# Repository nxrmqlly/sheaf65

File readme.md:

# sheaf65 🌊

A barebones, hackable, opinionated, ansi 65% layout  keyboard. The `Backspace` key and the `Grave` key swapped due to personal preferences.

The Keyboard is designed to be very bare bones and it is basically 3 layers - The switchplate (top), The PCB (Middle),
and The Backplate (Bottom) - kind of like a sandwich mounted keyboard.

The switchplate ("plate") and the backplate are to be 3D printed and engineered.
The whole "sandwich" is held together with 10 M2x10mm brass spacers and one M2x6mm brass spacer.

I also took the liberty to add two knobs and an OLED display to the keyboard because... why not?

## TL;DR for busy people

A simple, hackable 65% keyboard
1. RP2040-powered
2. Fully Hotswap (TTC Pokayoke V2)
3. 0.91" OLED Screen
4. Dual Rotary Encoders (Knobs)
5. QMK firmware (VIA soon)
6. Sandwich Mounted (3-stacked-layer)

Built because I wanted something fun and unique... with knobs.

## Why?
I wanted a nice keyboard, and decided that making one for myself would be a fun challenge to pursue.
I wanted a unique yet sleek looking keyboard that somewhat resembles the idea of a through hole keybaord kit minus the ugly visible diodes.
Also, no such THT keyboard kit did hotswap sockets (I know the sockets are SMD but you get me) so there's that.

## Microcontroller / Devboard
I used an Generic ProMicro RP2040 chip which is basically an Pi RP2040 in a somewhat a ProMicro layout, I found it on robu and I thought it was perfect so I went with it!. 

The devboard is THT soldered and mounted onto the keyboard, in full display, sort of like nibble65 keyboard but horizontal.

## The PCB

The PCB was made in the best software ever (for legal reasons that's a joke) called **KiCad**, it was straightforward enough but I think a good software helps a ton! Also, I'm taking on SMD soldering by including TTC Pokayoke hotswap sockets in this!

Here are some screenshots:

| What               | Image                               |
|--------------------|-------------------------------------|
| Schematic          | |
| PCB (B.silk hidden)|             |
| PCB 3D Model       ||

## The "Case"

I designed the case in Autodesk Fusion (formerly Fusion360) - good software!
The case is not really a case, its just two plates, one backplate and one switchplate

| What               | Image                                        |
|--------------------|----------------------------------------------|
| CAD Assembly       | |

## WTF is that design? (Design Credits + more)

The inspiration for this kind of keyboard case (or the whole thing in general) comes from though-hole keyboard kits like:
- mercuito40 (for the switchplate and mounting)
- gingham65 (mounting)
- nibble65 (embracing the exposed MCU design)
- my wack brain (for two knobs)
- also thanks to [somepin](https://www.printables.com/@somepin) for the [3d printed keyboard feet](https://www.printables.com/model/876658-mechanical-keyboard-cone-feet/files)
- **Honorable mention:**
>*reviewer (#fallout-checkpoint): ...I also think this would look sick with under glow... maybe consider that*
>Yeah no, the keyboard was NoRGB by choice, I like NoRGB setups

However, I didn't really like the exposed ugly diodes on the top, so I opted for a neat silkscreen instead which I designed in **Figma** (I know it isnt the correct tool for the job but whatever really)

> (find the custom silkscreen footprints [here](./kicad/footprints/art.pretty/))

## Keyboard Parts

Straightforward really, the switches, keycaps - they're all personal preference, so, heres my preference:

1. **Switches**: Nothing really beats the **Keygeek x MZ Y3 Linear Switches** for me, they're the perfect mix of thock (not as much as the Y2) and just enough creamy sound
2. **Keycaps**: PBT Clone Keycaps, nothing technical here, just Cherry Profile because I'm boring.
3. **Stabilizers**: i may have cheaped out, but the **Durock Plate-Mount Stabilizers** will work out for me.
4. **Hotswap**: The PCB is designed for TTC Pokayoke V2 hotswap sockets, so customizability is infinite!
5. **The "Case"**: The Hardware/CAD directory has both KeyboardPlate and Backplate STEP files, with their _3DP suffixed variants which are meant for 3D printing as they are filleted.

But really though, switches and keycaps are very personal and well, I can't really decide for you but all I can say is that I saw a thousand videos before settline on what I did.

## Firmware

Nothing too fancy here, just QMK (I fought with qmk for HOURS)

I plan to add VIA support soon :tm:

## The BOM

I would create a markdown table but I'm lazy... full breakdown in
[bom.csv here](./Hardware/bom/bom.csv)

> Costs \~₹10619 (~$124)

Somehow the BOM was fun to write!

## How to build it IRL

1. Spend some $$$ to get the parts from the BOM
2. Get your PCB fabricated and case 3D printed or machined (if 3D printing use the _3DP suffixed CAD files)
3. Solder Hotswap sockets on the back of the PCB and the through hole diodes too.
4. Solder header pins onto the MCU and that onto the PCB
5. Secure the 6mm stanoffs onto the countersunk holes on the backplate and the 10mm standoffs on the rest of the holes
6. Connect your switches to the plate and PCB
7. Slide the PCB into the standoffs and secure the plate with screws.

## License
The hardware (PCB, CAD Parts, Footprints) are licensed under `CERN Open Hardware Licence Version 2 - Strongly Reciprocal` 
which means, you're all-right to copy my work and use it in yours but you must disclose your source code and project files to opensource platforms if you use my work. See [LICENSE](LICENSE)

Firmware is QMK so, it is licensed under `GNU General Public License v2` (see [LICENSE-GPL](LICENSE-GPL))

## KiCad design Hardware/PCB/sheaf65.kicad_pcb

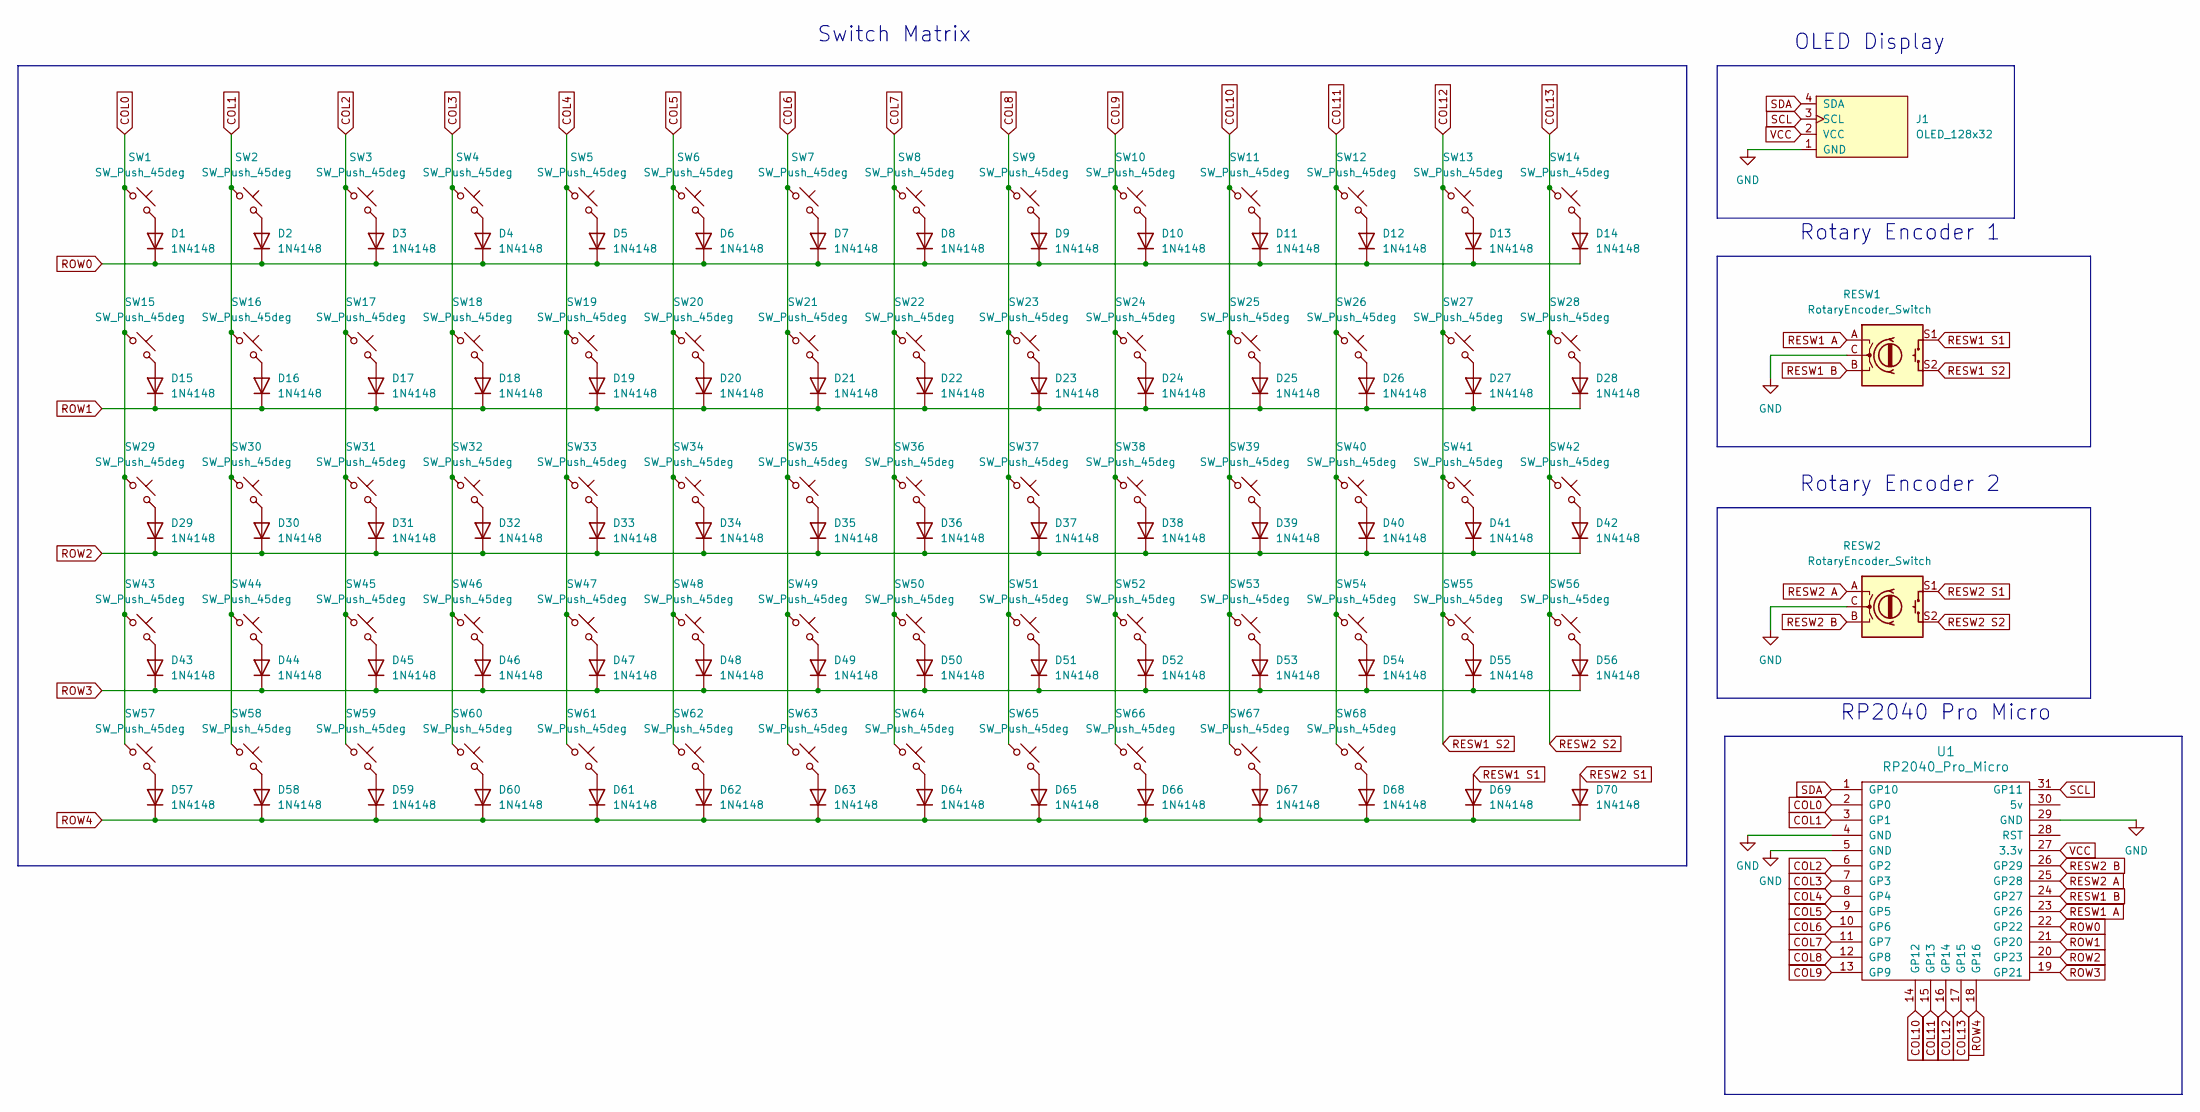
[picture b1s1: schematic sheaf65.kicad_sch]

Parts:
D1, D2, D3, D4, D5, D6, D7, D8, D9, D10, D11, D12, D13, D14, D15, D16, D17, D18, D19, D20, D21, D22, D23, D24, D25, D26, D27, D28, D29, D30, D31, D32, D33, D34, D35, D36, D37, D38, D39, D40, D41, D42, D43, D44, D45, D46, D47, D48, D49, D50, D51, D52, D53, D54, D55, D56, D57, D58, D59, D60, D61, D62, D63, D64, D65, D66, D67, D68, D69, D70: 1N4148; D_DO-35_SOD27_P7.62mm_Horizontal
J1: OLED_128x32; SSD1306-0.91-OLED-4pin-128x32
RESW1, RESW2: RotaryEncoder_Switch; RotaryEncoder_Alps_EC11E-Switch_Vertical_H20mm
SW1, SW2, SW3, SW4, SW5, SW6, SW7, SW8, SW9, SW10, SW11, SW12, SW13, SW15, SW17, SW18, SW19, SW20, SW21, SW22, SW23, SW24, SW25, SW26, SW27, SW28, SW30, SW32, SW33, SW34, SW35, SW36, SW37, SW38, SW39, SW40, SW41, SW42, SW44, SW46, SW47, SW48, SW49, SW50, SW51, SW52, SW53, SW54, SW55, SW57, SW58, SW63, SW64, SW65, SW66, SW67, SW68: SW_Push_45deg; SW_Hotswap_Kailh_MX_1.00u
SW14: SW_Push_45deg; SW_Hotswap_Kailh_MX_2.00u
SW16, SW29: SW_Push_45deg; SW_Hotswap_Kailh_MX_1.50u
SW31, SW56: SW_Push_45deg; SW_Hotswap_Kailh_MX_1.75u
SW43, SW45: SW_Push_45deg; SW_Hotswap_Kailh_MX_2.25u
SW59, SW60, SW61: SW_Push_45deg; SW_Hotswap_Kailh_MX_1.25u
SW62: SW_Push_45deg; SW_Hotswap_Kailh_MX_6.25u
U1: RP2040_Pro_Micro

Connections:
COL0: SW1.1, SW15.1, SW29.1, SW43.1, SW57.1, U1.2 (GP0)
COL1: SW2.1, SW16.1, SW30.1, SW44.1, SW58.1, U1.3 (GP1)
COL2: SW3.1, SW17.1, SW31.1, SW45.1, SW59.1, U1.6 (GP2)
COL3: SW4.1, SW18.1, SW32.1, SW46.1, SW60.1, U1.7 (GP3)
COL4: SW5.1, SW19.1, SW33.1, SW47.1, SW61.1, U1.8 (GP4)
COL5: SW6.1, SW20.1, SW34.1, SW48.1, SW62.1, U1.9 (GP5)
COL6: SW7.1, SW21.1, SW35.1, SW49.1, SW63.1, U1.10 (GP6)
COL7: SW8.1, SW22.1, SW36.1, SW50.1, SW64.1, U1.11 (GP7)
COL8: SW9.1, SW23.1, SW37.1, SW51.1, SW65.1, U1.12 (GP8)
COL9: SW10.1, SW24.1, SW38.1, SW52.1, SW66.1, U1.13 (GP9)
COL10: SW11.1, SW25.1, SW39.1, SW53.1, SW67.1, U1.14 (GP12)
COL11: SW12.1, SW26.1, SW40.1, SW54.1, SW68.1, U1.15 (GP13)
COL12: RESW1.S2, SW13.1, SW27.1, SW41.1, SW55.1, U1.16 (GP14)
COL13: RESW2.S2, SW14.1, SW28.1, SW42.1, SW56.1, U1.17 (GP15)
GND: J1.1 (GND), RESW1.C, RESW2.C, U1.4 (GND), U1.5 (GND), U1.29 (GND)
unnamed: D1.2 (A), SW1.2
unnamed: D2.2 (A), SW2.2
unnamed: D3.2 (A), SW3.2
unnamed: D4.2 (A), SW4.2
unnamed: D5.2 (A), SW5.2
unnamed: D6.2 (A), SW6.2
unnamed: D7.2 (A), SW7.2
unnamed: D8.2 (A), SW8.2
unnamed: D9.2 (A), SW9.2
unnamed: D10.2 (A), SW10.2
unnamed: D11.2 (A), SW11.2
unnamed: D12.2 (A), SW12.2
unnamed: D13.2 (A), SW13.2
unnamed: D14.2 (A), SW14.2
unnamed: D15.2 (A), SW15.2
unnamed: D16.2 (A), SW16.2
unnamed: D17.2 (A), SW17.2
unnamed: D18.2 (A), SW18.2
unnamed: D19.2 (A), SW19.2
unnamed: D20.2 (A), SW20.2
unnamed: D21.2 (A), SW21.2
unnamed: D22.2 (A), SW22.2
unnamed: D23.2 (A), SW23.2
unnamed: D24.2 (A), SW24.2
unnamed: D25.2 (A), SW25.2
unnamed: D26.2 (A), SW26.2
unnamed: D27.2 (A), SW27.2
unnamed: D28.2 (A), SW28.2
unnamed: D29.2 (A), SW29.2
unnamed: D30.2 (A), SW30.2
unnamed: D31.2 (A), SW31.2
unnamed: D32.2 (A), SW32.2
unnamed: D33.2 (A), SW33.2
unnamed: D34.2 (A), SW34.2
unnamed: D35.2 (A), SW35.2
unnamed: D36.2 (A), SW36.2
unnamed: D37.2 (A), SW37.2
unnamed: D38.2 (A), SW38.2
unnamed: D39.2 (A), SW39.2
unnamed: D40.2 (A), SW40.2
unnamed: D41.2 (A), SW41.2
unnamed: D42.2 (A), SW42.2
unnamed: D43.2 (A), SW43.2
unnamed: D44.2 (A), SW44.2
unnamed: D45.2 (A), SW45.2
unnamed: D46.2 (A), SW46.2
unnamed: D47.2 (A), SW47.2
unnamed: D48.2 (A), SW48.2
unnamed: D49.2 (A), SW49.2
unnamed: D50.2 (A), SW50.2
unnamed: D51.2 (A), SW51.2
unnamed: D52.2 (A), SW52.2
unnamed: D53.2 (A), SW53.2
unnamed: D54.2 (A), SW54.2
unnamed: D55.2 (A), SW55.2
unnamed: D56.2 (A), SW56.2
unnamed: D57.2 (A), SW57.2
unnamed: D58.2 (A), SW58.2
unnamed: D59.2 (A), SW59.2
unnamed: D60.2 (A), SW60.2
unnamed: D61.2 (A), SW61.2
unnamed: D62.2 (A), SW62.2
unnamed: D63.2 (A), SW63.2
unnamed: D64.2 (A), SW64.2
unnamed: D65.2 (A), SW65.2
unnamed: D66.2 (A), SW66.2
unnamed: D67.2 (A), SW67.2
unnamed: D68.2 (A), SW68.2
RESW1 A: RESW1.A, U1.23 (GP26)
RESW1 B: RESW1.B, U1.24 (GP27)
RESW1 S1: D69.2 (A), RESW1.S1
RESW2 A: RESW2.A, U1.25 (GP28)
RESW2 B: RESW2.B, U1.26 (GP29)
RESW2 S1: D70.2 (A), RESW2.S1
ROW0: D1.1 (K), D2.1 (K), D3.1 (K), D4.1 (K), D5.1 (K), D6.1 (K), D7.1 (K), D8.1 (K), D9.1 (K), D10.1 (K), D11.1 (K), D12.1 (K), D13.1 (K), D14.1 (K), U1.22 (GP22)
ROW1: D15.1 (K), D16.1 (K), D17.1 (K), D18.1 (K), D19.1 (K), D20.1 (K), D21.1 (K), D22.1 (K), D23.1 (K), D24.1 (K), D25.1 (K), D26.1 (K), D27.1 (K), D28.1 (K), U1.21 (GP20)
ROW2: D29.1 (K), D30.1 (K), D31.1 (K), D32.1 (K), D33.1 (K), D34.1 (K), D35.1 (K), D36.1 (K), D37.1 (K), D38.1 (K), D39.1 (K), D40.1 (K), D41.1 (K), D42.1 (K), U1.20 (GP23)
ROW3: D43.1 (K), D44.1 (K), D45.1 (K), D46.1 (K), D47.1 (K), D48.1 (K), D49.1 (K), D50.1 (K), D51.1 (K), D52.1 (K), D53.1 (K), D54.1 (K), D55.1 (K), D56.1 (K), U1.19 (GP21)
ROW4: D57.1 (K), D58.1 (K), D59.1 (K), D60.1 (K), D61.1 (K), D62.1 (K), D63.1 (K), D64.1 (K), D65.1 (K), D66.1 (K), D67.1 (K), D68.1 (K), D69.1 (K), D70.1 (K), U1.18 (GP16)
SCL: J1.3 (SCL), U1.31 (GP11)
SDA: J1.4 (SDA), U1.1 (GP10)
VCC: J1.2 (VCC), U1.27 (3.3v)

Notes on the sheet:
RP2040 Pro Micro
Rotary Encoder 2
Switch Matrix
Rotary Encoder 1
OLED Display

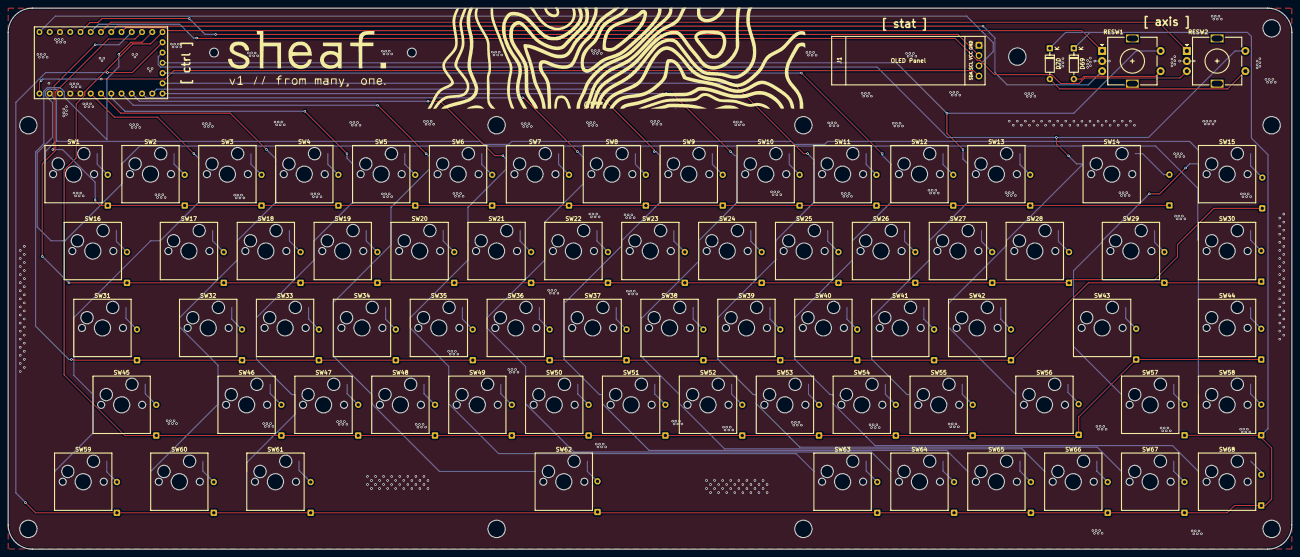
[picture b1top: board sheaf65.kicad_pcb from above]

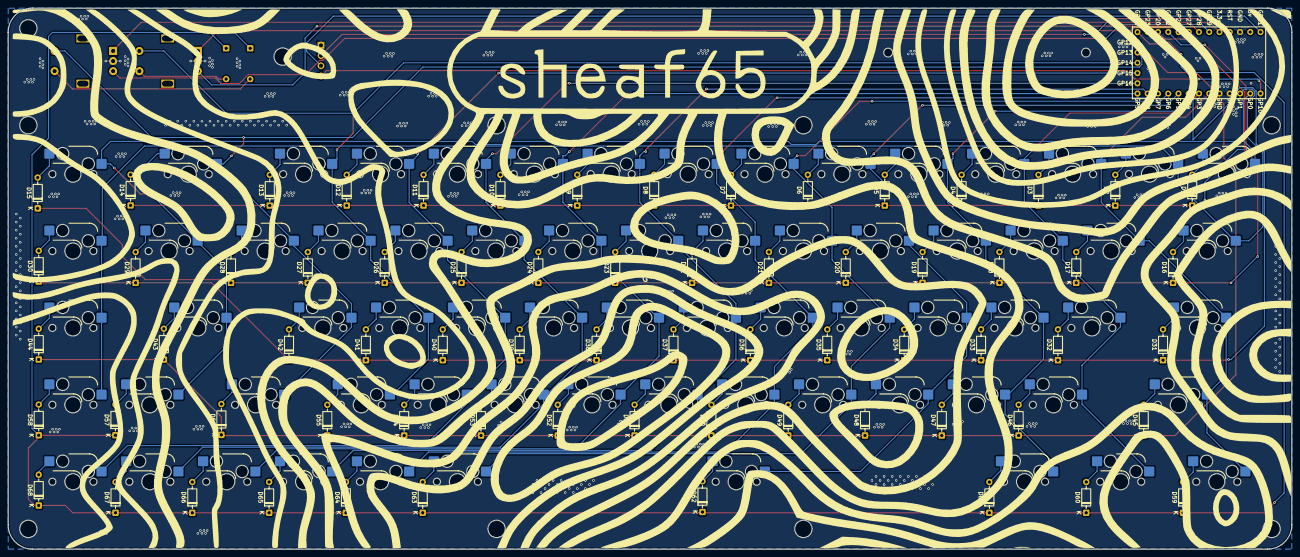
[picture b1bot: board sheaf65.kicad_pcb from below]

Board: 2 copper layers, 318.0 x 134.0 mm, 142 parts (68 on the bottom side), 97 nets.

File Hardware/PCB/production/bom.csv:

Designator,Footprint,Quantity,Value,LCSC Part #
"D1, D10, D11, D12, D13, D14, D15, D16, D17, D18, D19, D2, D20, D21, D22, D23, D24, D25, D26, D27, D28, D29, D3, D30, D31, D32, D33, D34, D35, D36, D37, D38, D39, D4, D40, D41, D42, D43, D44, D45, D46, D47, D48, D49, D5, D50, D51, D52, D53, D54, D55, D56, D57, D58, D59, D6, D60, D61, D62, D63, D64, D65, D66, D67, D68, D69, D7, D70, D8, D9",D_DO-35_SOD27_P7.62mm_Horizontal,70,1N4148,
J1,SSD1306-0.91-OLED-4pin-128x32,1,OLED_128x32,
"RESW1, RESW2",RotaryEncoder_Alps_EC11E-Switch_Vertical_H20mm,2,RotaryEncoder_Switch,
"SW1, SW10, SW11, SW12, SW13, SW15, SW17, SW18, SW19, SW2, SW20, SW21, SW22, SW23, SW24, SW25, SW26, SW27, SW28, SW3, SW30, SW32, SW33, SW34, SW35, SW36, SW37, SW38, SW39, SW4, SW40, SW41, SW42, SW44, SW46, SW47, SW48, SW49, SW5, SW50, SW51, SW52, SW53, SW54, SW55, SW57, SW58, SW6, SW63, SW64, SW65, SW66, SW67, SW68, SW7, SW8, SW9",SW_Hotswap_Kailh_MX_1.00u,57,SW_Push_45deg,
SW14,SW_Hotswap_Kailh_MX_2.00u,1,SW_Push_45deg,
"SW16, SW29",SW_Hotswap_Kailh_MX_1.50u,2,SW_Push_45deg,
"SW31, SW56",SW_Hotswap_Kailh_MX_1.75u,2,SW_Push_45deg,
"SW43, SW45",SW_Hotswap_Kailh_MX_2.25u,2,SW_Push_45deg,
"SW59, SW60, SW61",SW_Hotswap_Kailh_MX_1.25u,3,SW_Push_45deg,
SW62,SW_Hotswap_Kailh_MX_6.25u,1,SW_Push_45deg,
U1,RP2040_Pro_Micro,1,RP2040_Pro_Micro,

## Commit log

2026-04-08 inital commit at 19h lol
2026-04-08 add readme
2026-04-08 add license
2026-04-13 add firmware
2026-04-13 add qmk firmware
2026-04-13 update readme and keymap
2026-04-13 update pcb mounting hole 11
2026-04-14 re-ad keymap.c (accidental delete)
2026-04-14 final update: cad, zine page, bom
2026-04-14 add .f3z archive
2026-04-14 add "why" to readme
2026-04-14 rename keyboooard to sheaf65
2026-04-14 add how to build to readme
2026-04-14 fix typo
2026-04-24 update: zine quality
2026-04-24 update: add keyboard feet, update CAD models, update BOM
2026-04-24 TTC PY V2 hotswap sockets
2026-04-24 update prices
2026-04-24 norgb design note
2026-04-25 tiny mistake fixed
2026-05-03 add printing to BOM
2026-05-03 update net cost in readme
2026-05-31 update GND and clean routes
